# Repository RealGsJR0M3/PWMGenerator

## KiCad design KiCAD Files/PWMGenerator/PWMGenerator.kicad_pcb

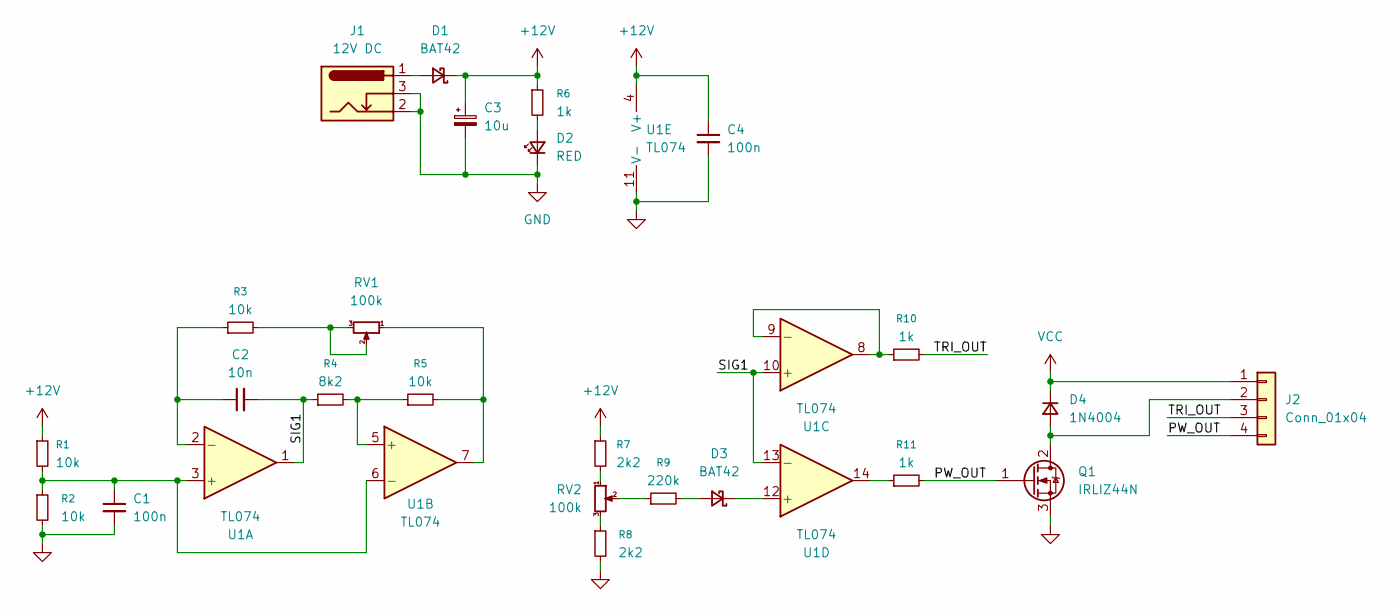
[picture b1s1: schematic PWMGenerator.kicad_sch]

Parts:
C1, C4: 100n; C_0805_2012Metric_Pad1.18x1.45mm_HandSolder
C2: 10n; C_0805_2012Metric_Pad1.18x1.45mm_HandSolder
C3: 10u; CP_Radial_D10.0mm_P5.00mm
D1, D3: BAT42; D_DO-35_SOD27_P7.62mm_Horizontal
D2: RED; LED_1206_3216Metric_Pad1.42x1.75mm_HandSolder
D4: 1N4004; D_DO-41_SOD81_P7.62mm_Horizontal
J1: 12V DC; TerminalBlock_MaiXu_MX126-5.0-02P_1x02_P5.00mm
J2: Conn_01x04; PinHeader_1x04_P2.54mm_Vertical
Q1: IRLIZ44N; TO-220F-3_Vertical
R1, R2, R3, R5: 10k; R_0805_2012Metric_Pad1.20x1.40mm_HandSolder
R4: 8k2; R_0805_2012Metric_Pad1.20x1.40mm_HandSolder
R6, R10, R11: 1k; R_0805_2012Metric_Pad1.20x1.40mm_HandSolder
R7, R8: 2k2; R_0805_2012Metric_Pad1.20x1.40mm_HandSolder
R9: 220k; R_0805_2012Metric_Pad1.20x1.40mm_HandSolder
RV1, RV2: 100k; Potentiometer_Piher_PC-16_Single_Horizontal
U1: TL074; SOIC-14_3.9x8.7mm_P1.27mm

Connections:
+12V: C3.1, C4.1, D1.1 (K), R1.1, R6.1, R7.1, U1.4 (V+)
/PW_OUT: J2.4, Q1.1 (G), R11.2
/SIG1: C2.2, R4.1, U1.1, U1.10 (+), U1.13 (-)
/TRI_OUT: J2.3, R10.2
GND: C1.2, C3.2, C4.2, D2.1 (K), J1.2, J1.3, Q1.3 (S), R2.2, R8.2, U1.11 (V-)
unnamed: D1.2 (A), J1.1
unnamed: D2.2 (A), R6.2
unnamed: D3.2 (A), R9.2
unnamed: D3.1 (K), U1.12 (+)
unnamed: D4.2 (A), J2.2, Q1.2 (D)
unnamed: R3.2, RV1.2, RV1.3
unnamed: R5.2, RV1.1, U1.7
unnamed: R7.2, RV2.1
unnamed: R8.1, RV2.3
unnamed: R9.1, RV2.2
unnamed: R11.1, U1.14
unnamed: C1.1, R1.2, R2.1, U1.3 (+), U1.6 (-)
unnamed: C2.1, R3.1, U1.2 (-)
unnamed: R4.2, R5.1, U1.5 (+)
unnamed: R10.1, U1.8, U1.9 (-)
VCC: D4.1 (K), J2.1

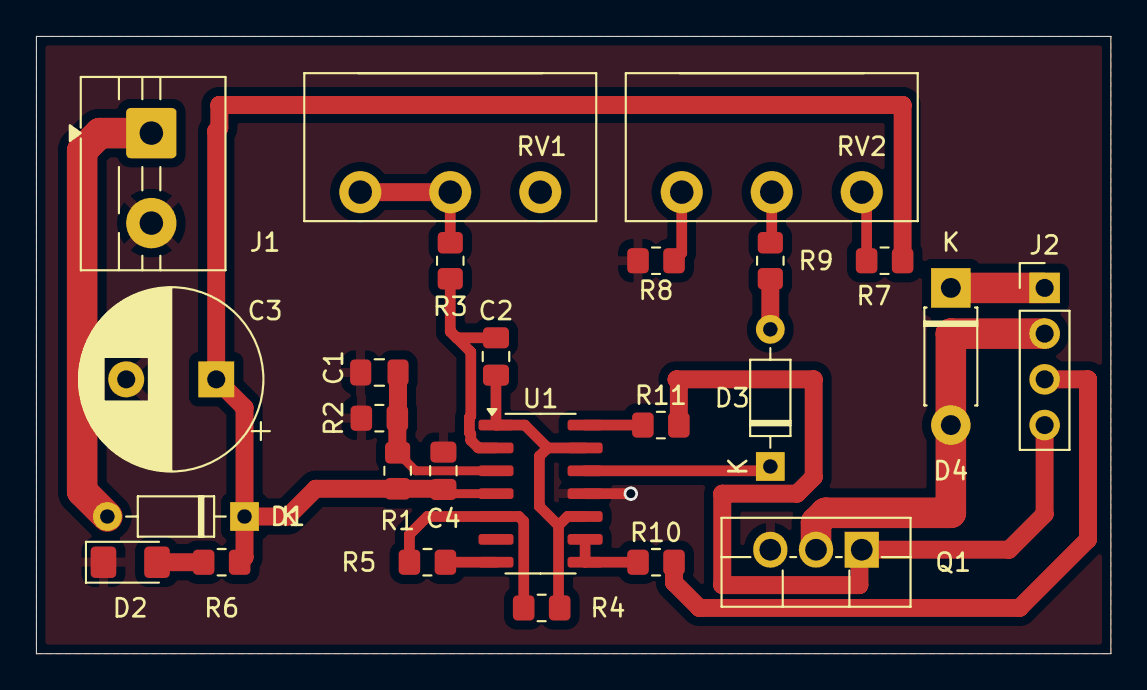
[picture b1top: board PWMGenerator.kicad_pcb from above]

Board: 2 copper layers, 59.7 x 34.3 mm, 25 parts (0 on the bottom side), 21 nets.

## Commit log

2025-04-26 KiCAD Schematic Diagram
2025-04-26 Updated Schematic
2025-04-28 Updated PCB Layout
